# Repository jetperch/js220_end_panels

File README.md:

# Joulescope Front Panels

Welcome to Joulescope™ JS220 front panel hardware design project.  This project 
contains the open source hardware designs for a variety of JS220 front
panels.  These front panels customize Joulescope so that it can more easily 
connect to your power supply and target device.
For more information on Joulescope, see 
[www.joulescope.com](https://www.joulescope.com).

The [Baseline PDF](eagle/fp_baseline/fp_baseline.pdf) show the board outline
and critical dimensions.

The 2x3 connector to the main board is
[Samtec TSM-103-01-S-DV-A](https://www.samtec.com/products/tsm-103-01-s-dv-a)
([Mouser](https://www.mouser.com/ProductDetail/Samtec/TSM-103-01-S-DV-A?qs=0lQeLiL1qyYnWtGorwZW9A%3D%3D),
[Digi-Key](https://www.digikey.com/en/products/detail/TSM-103-01-S-DV-A/TSM-103-01-S-DV-A-ND/2685555))

The boards have been fabricated using PCBWay. 
Here are the order notes ([example](pcbway_order.png)):

* Size: 95 x 24.7 mm
* FR-4, TG 150-160, 1.6 thick, 6/6, 0.3 mm min hole size
* Solder Mask: Black, White silkscreen
* Surface Finish: HASL lead free, do NOT check accept ENIG substitution
* Finished Copper 1 oz

Special requests text:
The front-side surface is cosmetic.  
Reject units with scratches and blemishes.
Place all markings on back, including pcb product number.
Add flammability rating marking on back, such as 94V-0.

## License

All Joulescope front-panel designs are released under the 
permissive Apache 2.0 license.

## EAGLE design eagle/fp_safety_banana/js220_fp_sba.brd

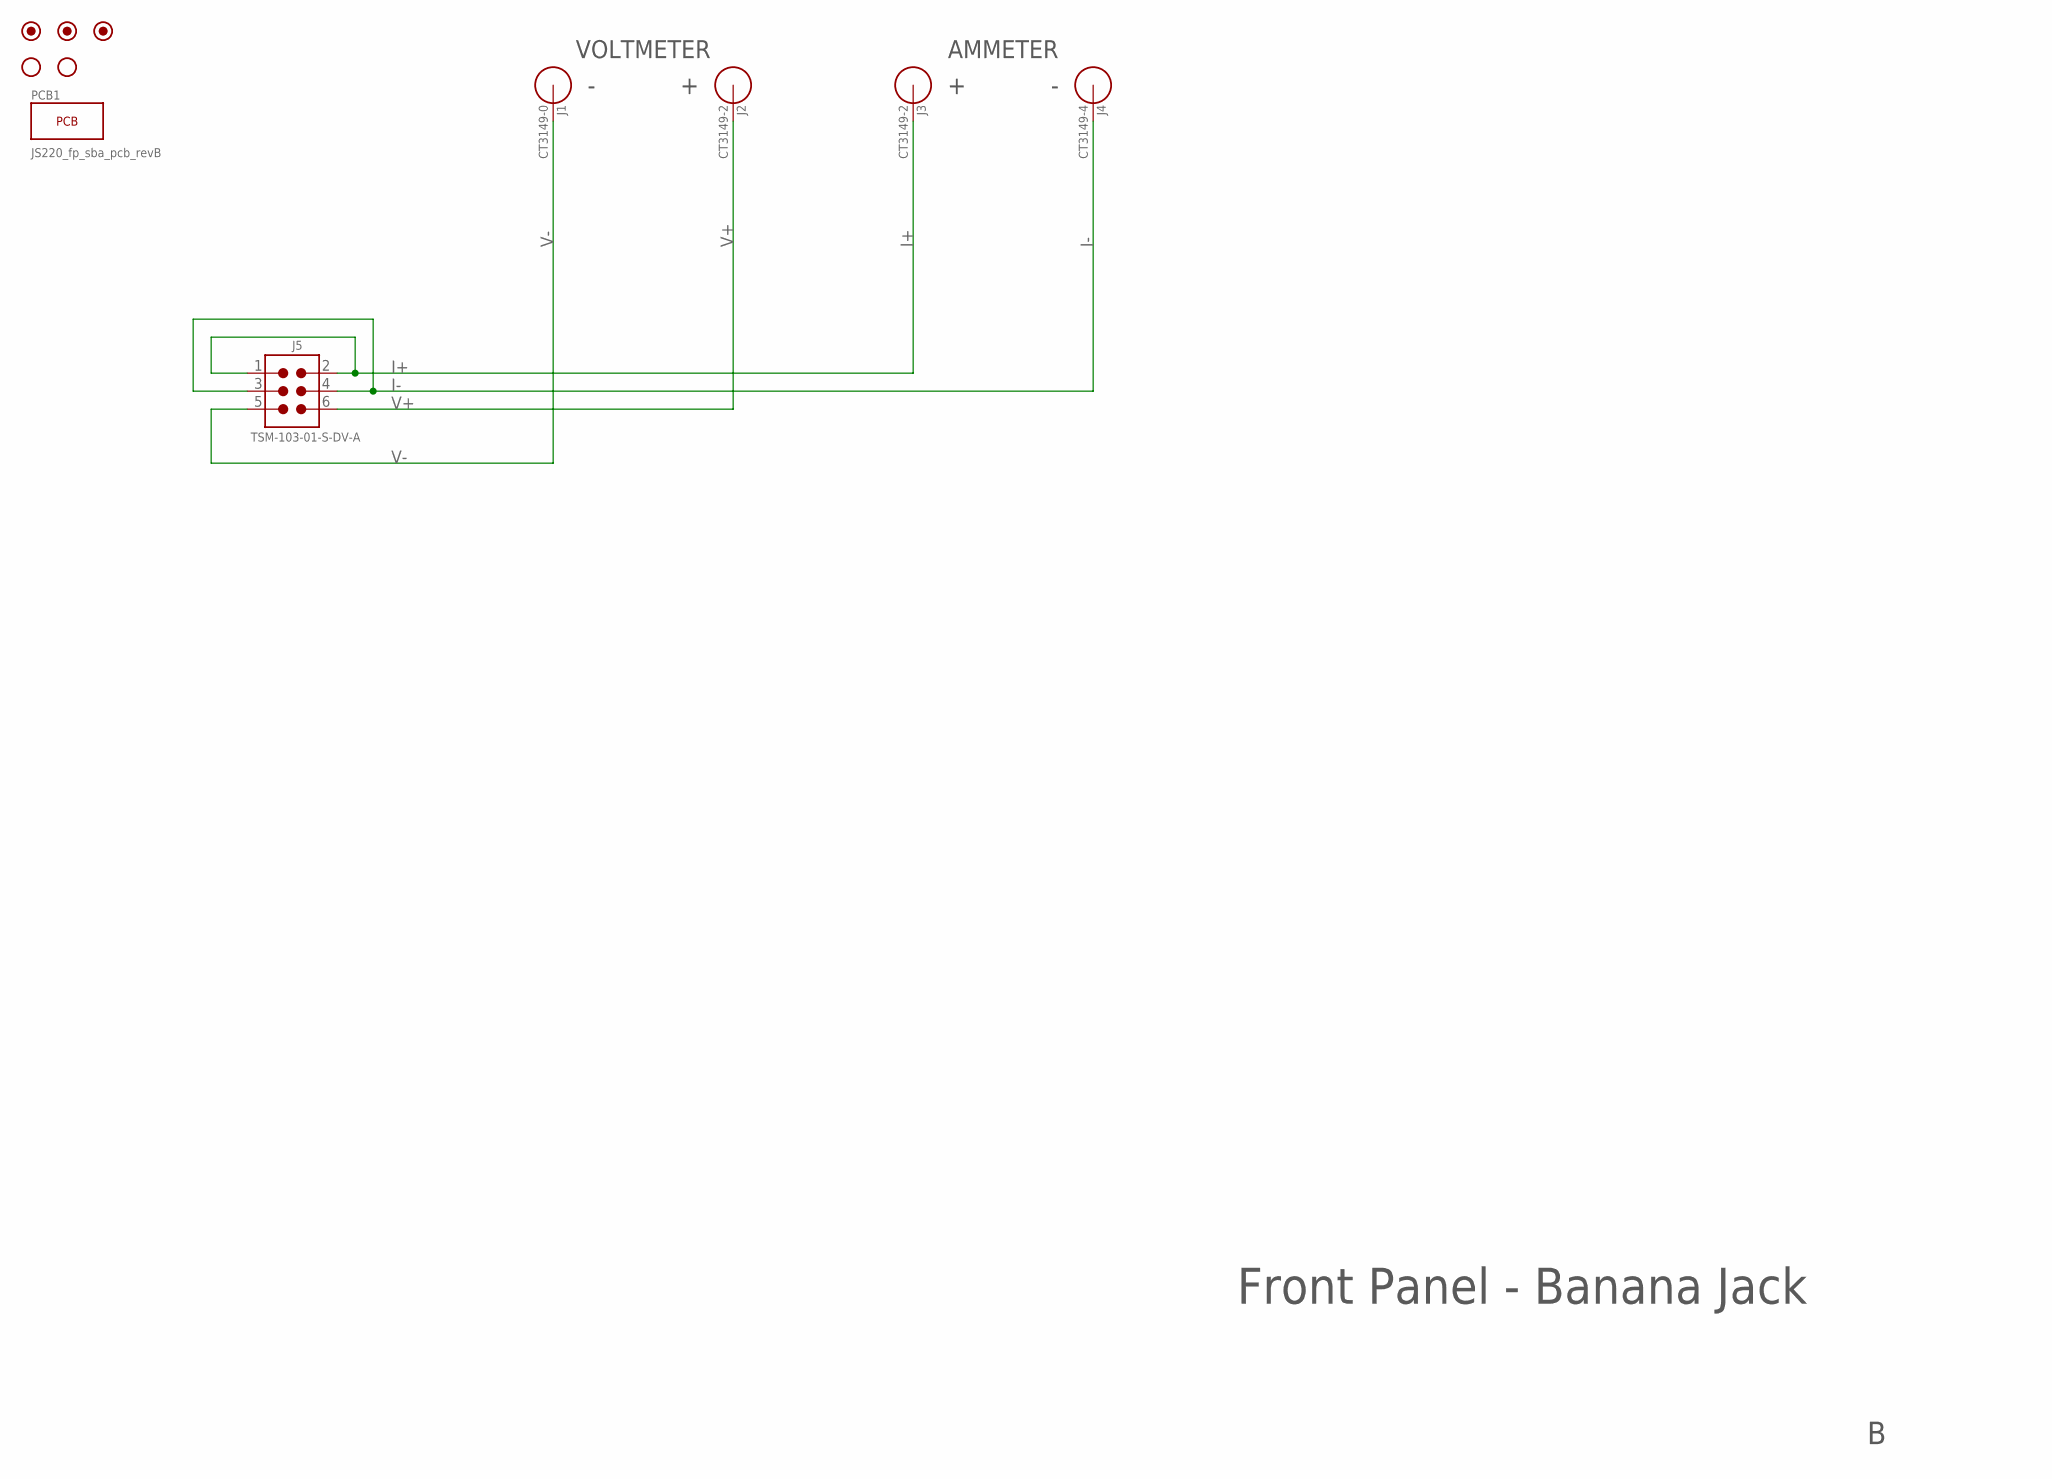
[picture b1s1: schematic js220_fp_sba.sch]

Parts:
FUD1, FUD2, FUD3: FIDUCIAL_1MM; FIDUCIAL_1MM_2MM
H1, H2: HOLE_#6_NORESTRICT; HOLE_3.5MM_NORESTRICT
J1: CT3149-0; CT3149
J2, J3: CT3149-2; CT3149
J4: CT3149-4; CT3149
J5: TSM-103-01-S-DV-A; CONN_0.1_3X2_MSA; MPN TSM-103-01-S-DV-A

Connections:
I+: J3.A, J5.1, J5.2
I-: J4.A, J5.3, J5.4
V+: J2.A, J5.6
V-: J1.A, J5.5

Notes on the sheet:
Front Panel - Banana Jack
+ -
AMMETER
VOLTMETER
- +

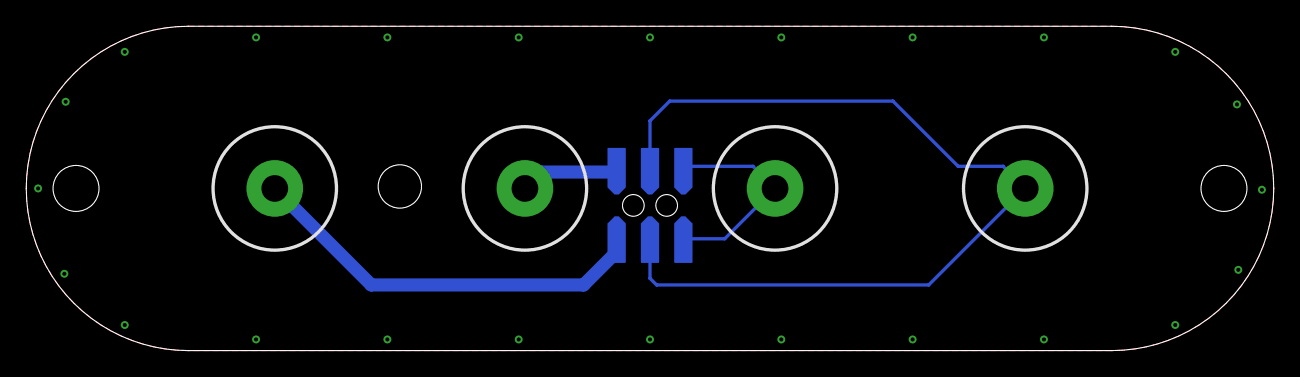
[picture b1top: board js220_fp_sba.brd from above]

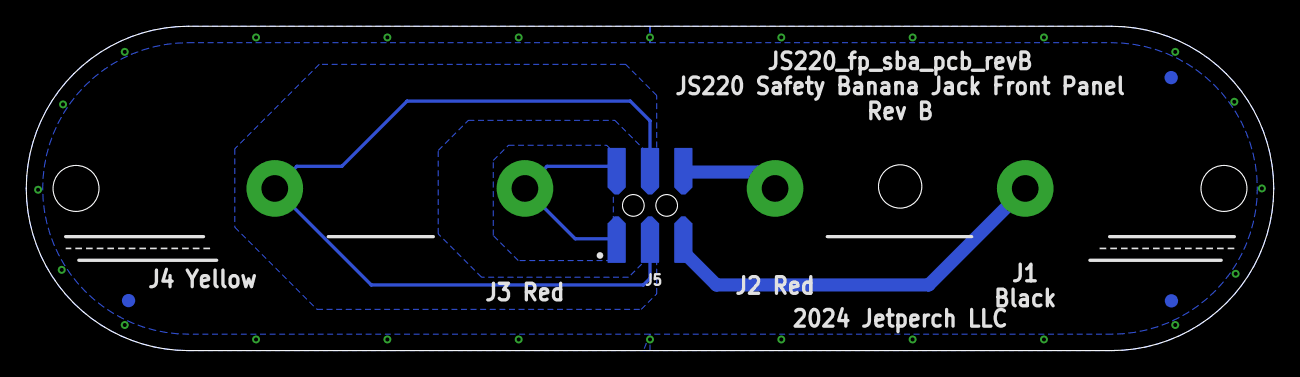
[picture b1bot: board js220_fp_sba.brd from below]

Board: 2 copper layers, 95.0 x 24.7 mm, 10 parts (4 on the bottom side), 4 nets.

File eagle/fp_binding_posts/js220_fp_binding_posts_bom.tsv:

Quantity	Part	Designators
2	111-0702-001	J2,J3
1	111-0703-001	J1
1	111-0707-001	J4
1	TSM-103-01-S-DV-A	J5
1	JS220_fp_binding_post_pcb_revC	PCB1

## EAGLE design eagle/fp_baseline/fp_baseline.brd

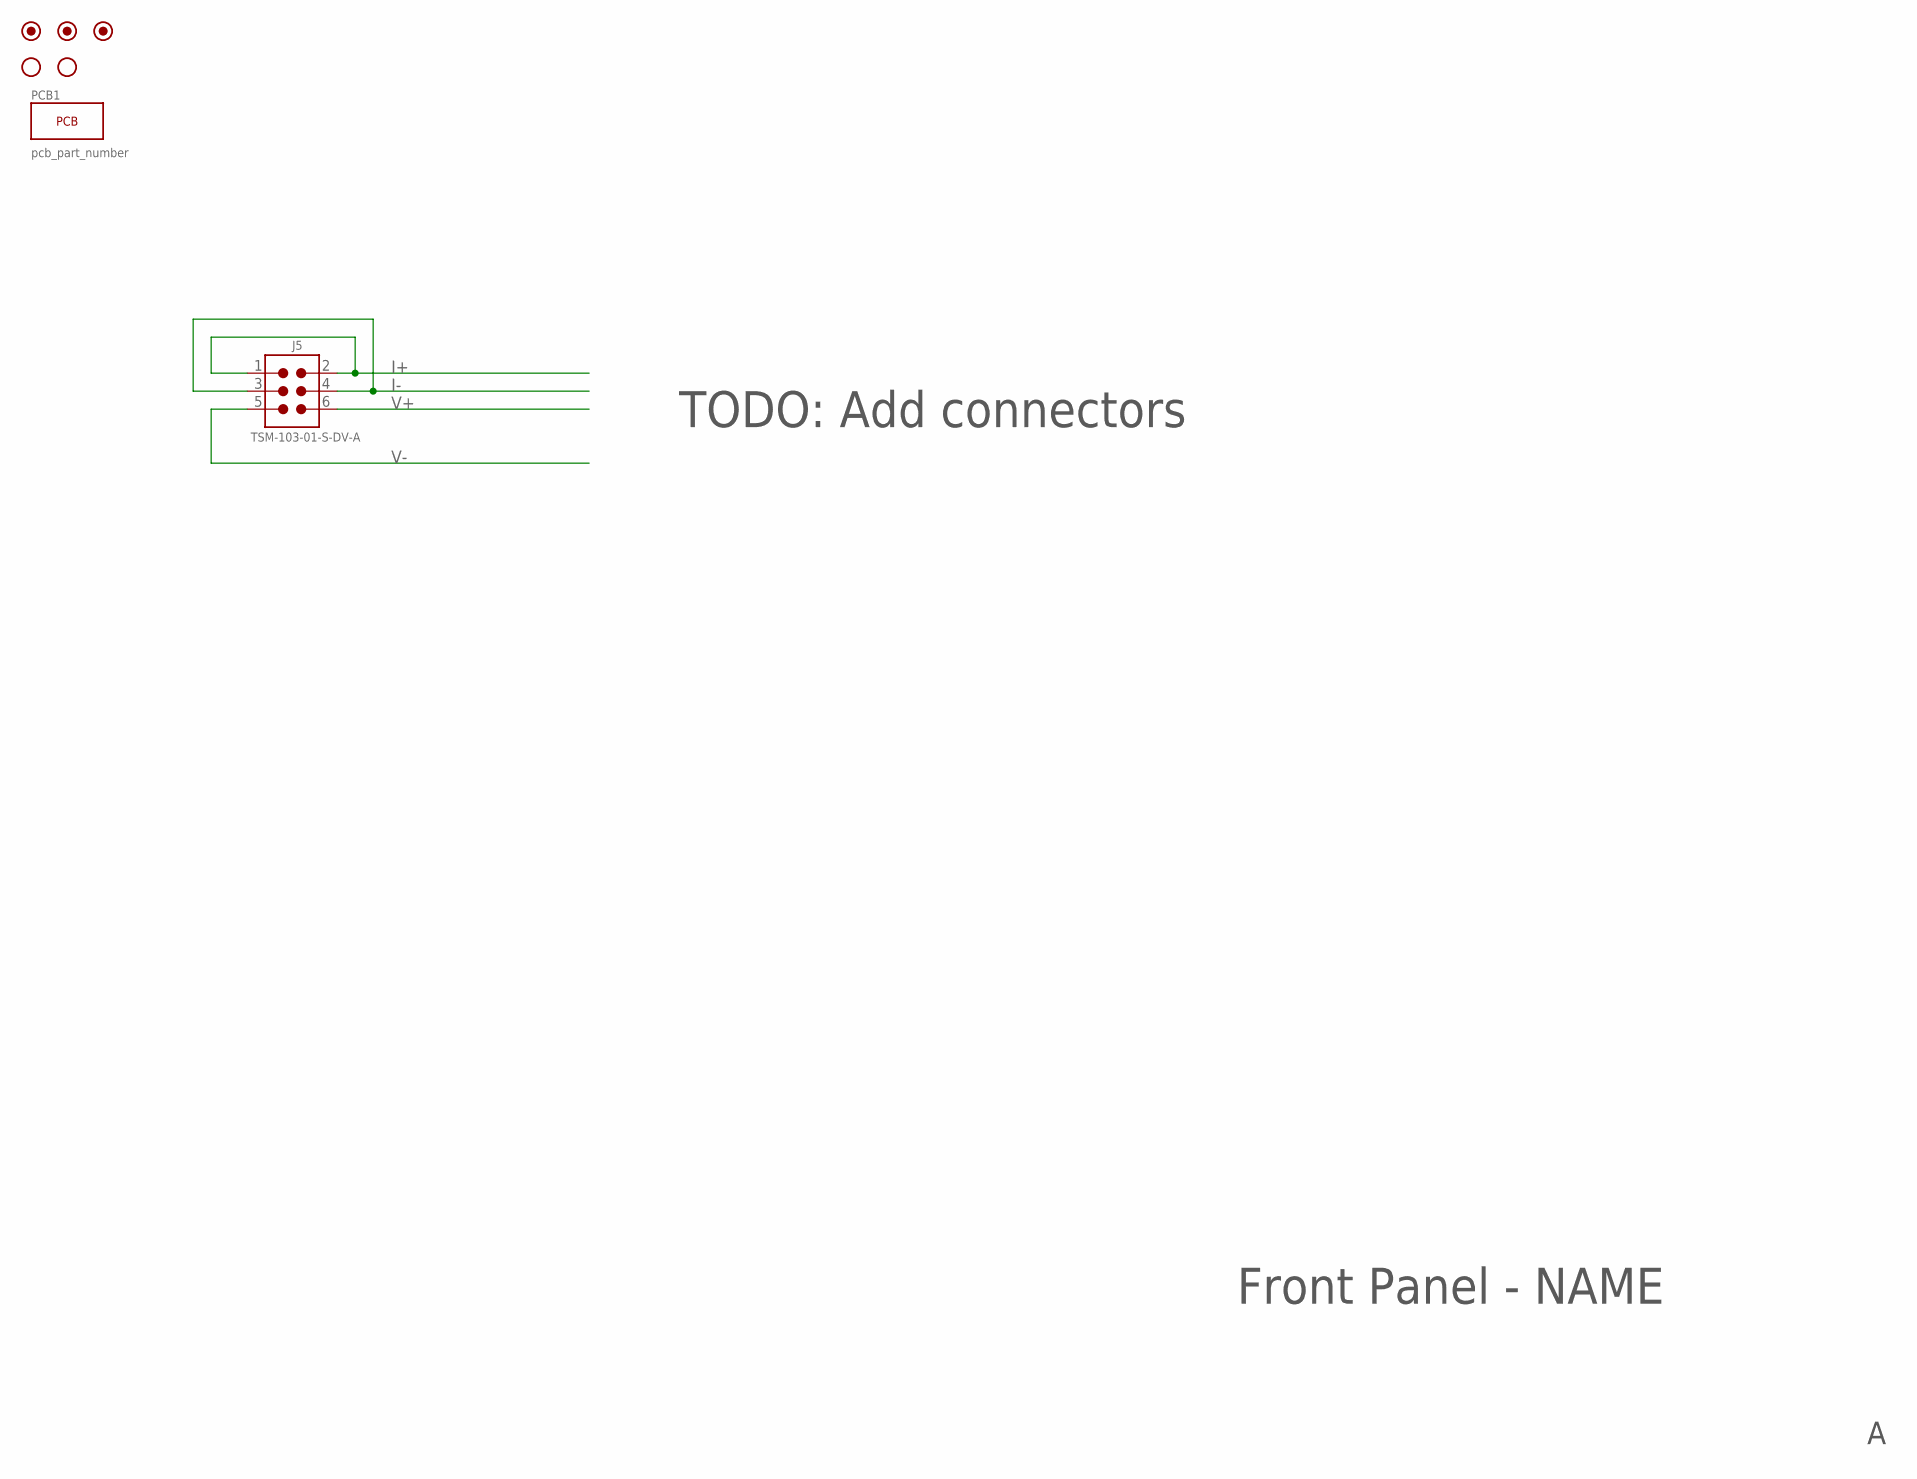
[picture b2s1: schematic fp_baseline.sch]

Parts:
FUD1, FUD2, FUD3: FIDUCIAL_1MM; FIDUCIAL_1MM_2MM
H1, H2: HOLE_#6_NORESTRICT; HOLE_3.5MM_NORESTRICT
J5: TSM-103-01-S-DV-A; CONN_0.1_3X2_MSA; MPN TSM-103-01-S-DV-A

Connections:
I+: J5.1, J5.2
I-: J5.3, J5.4
V+: J5.6
V-: J5.5

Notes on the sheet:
Front Panel - NAME
TODO: Add connectors

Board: 2 copper layers, 6 parts (4 on the bottom side), 2 nets, no tracks yet.

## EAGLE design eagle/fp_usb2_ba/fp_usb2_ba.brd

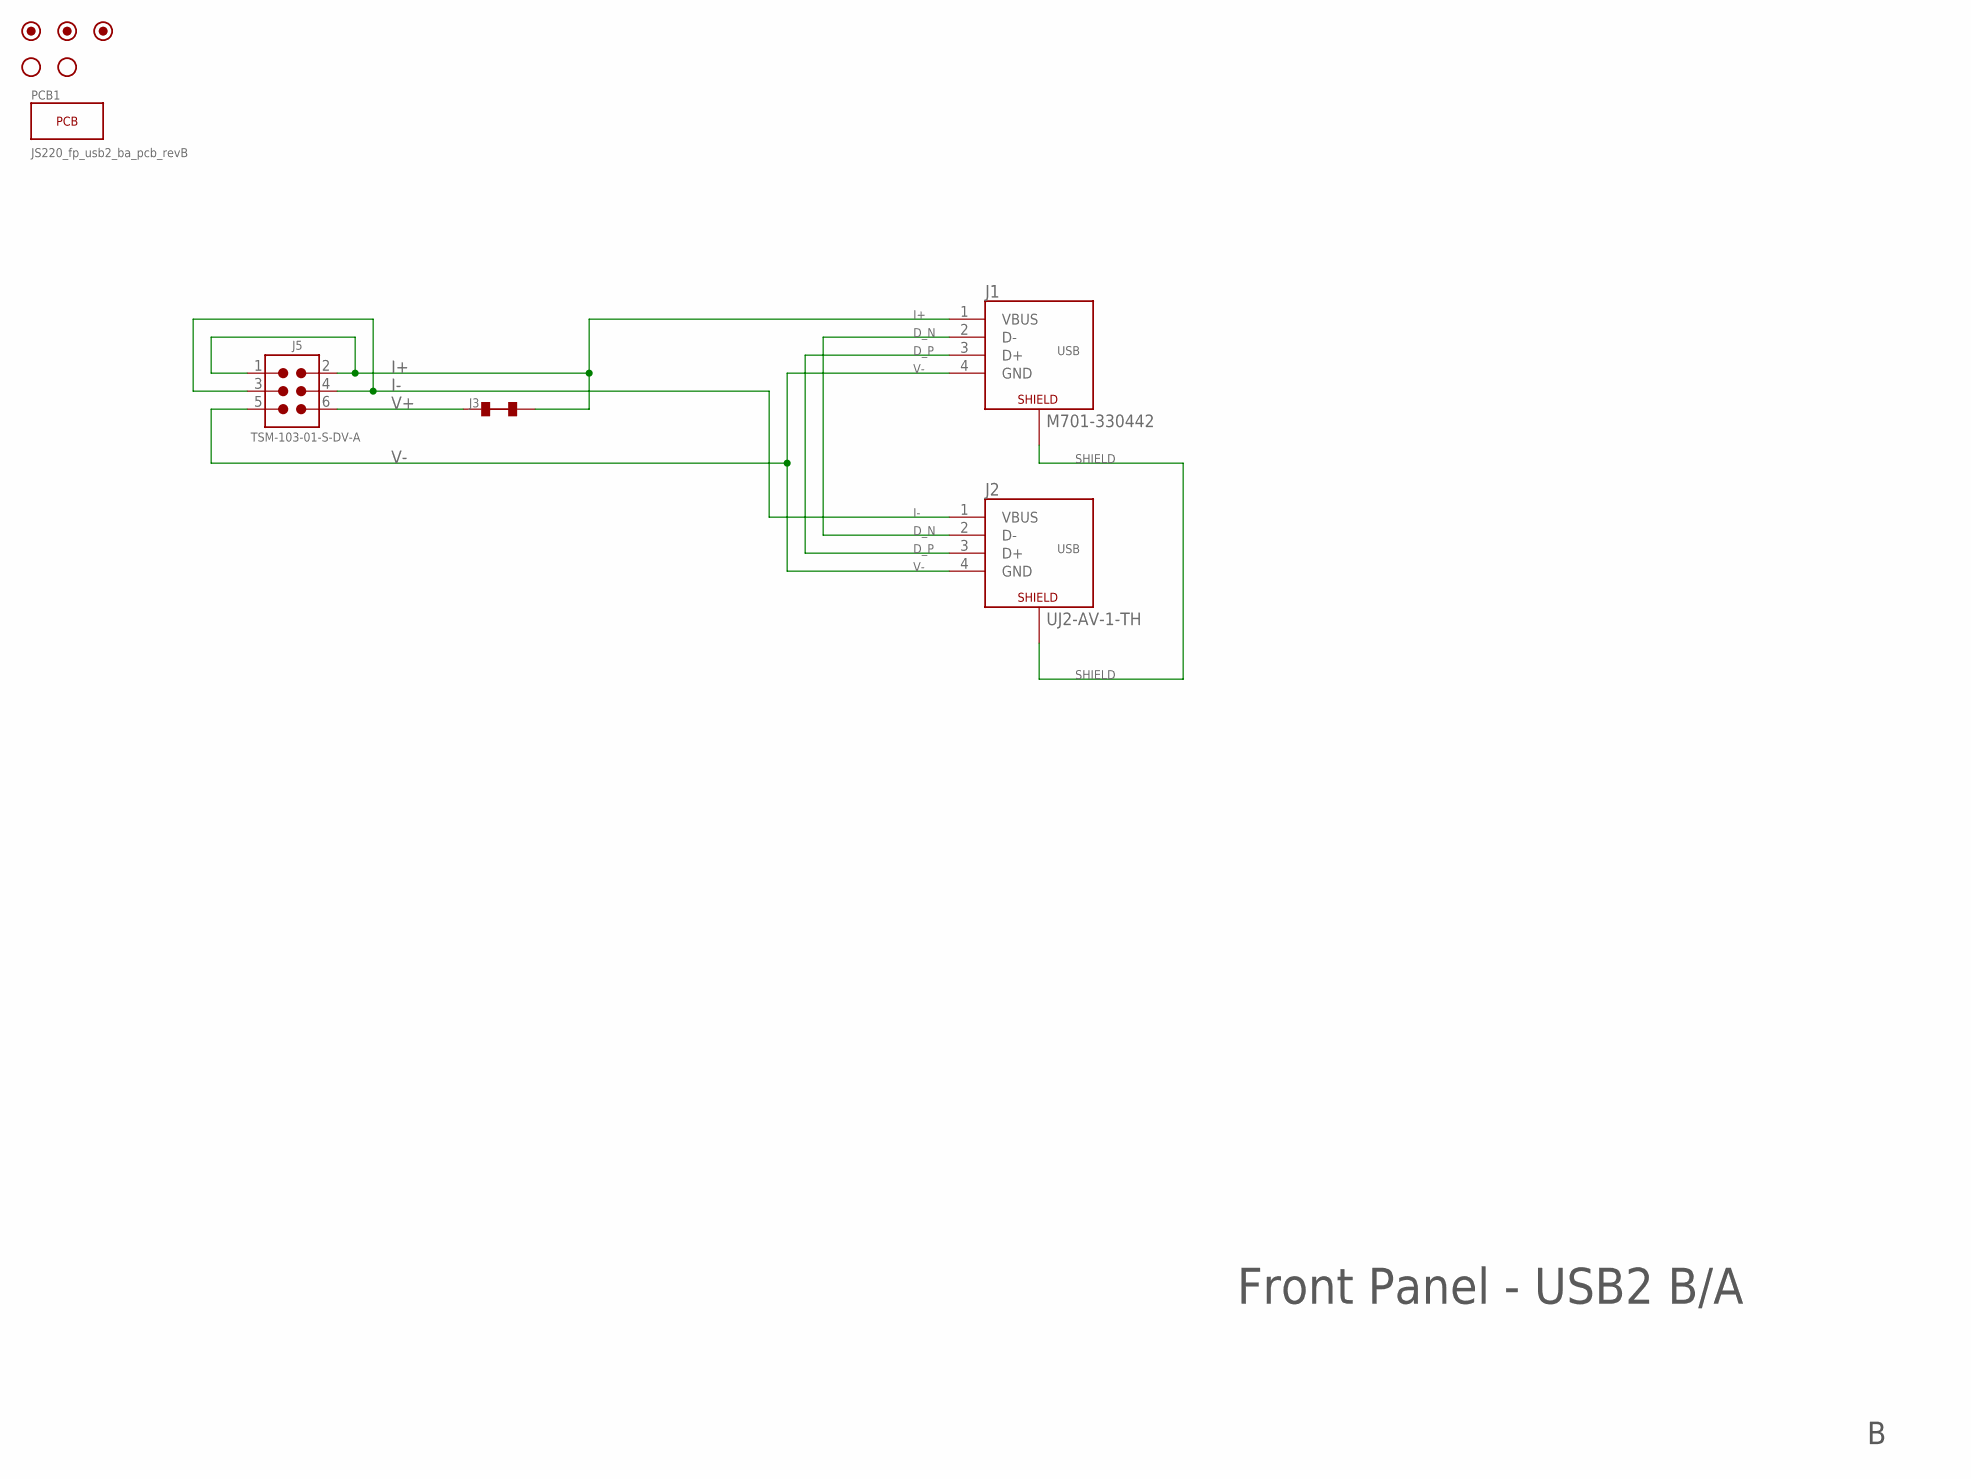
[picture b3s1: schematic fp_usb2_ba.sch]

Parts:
FUD1, FUD2, FUD3: FIDUCIAL_1MM; FIDUCIAL_1MM_2MM
H1, H2: HOLE_#6_NORESTRICT; HOLE_3.5MM_NORESTRICT
J1: M701-330442; USB-B-VTH
J2: UJ2-AV-1-TH; USB-A-VTH
J3: TRACE_CUT0603; J0603
J5: TSM-103-01-S-DV-A; CONN_0.1_3X2_MSA; MPN TSM-103-01-S-DV-A

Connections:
D_N: J1.2 (D-), J2.2 (D-)
D_P: J1.3 (D+), J2.3 (D+)
I+: J1.1 (VBUS), J3.2, J5.1, J5.2
I-: J2.1 (VBUS), J5.3, J5.4
SHIELD: J1.SHIELD@1 (SHIELD), J1.SHIELD@3 (SHIELD), J2.SHIELD@1 (SHIELD), J2.SHIELD@3 (SHIELD)
V+: J3.1, J5.6
V-: J1.4 (GND), J2.4 (GND), J5.5

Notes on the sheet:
Front Panel - USB2 B/A

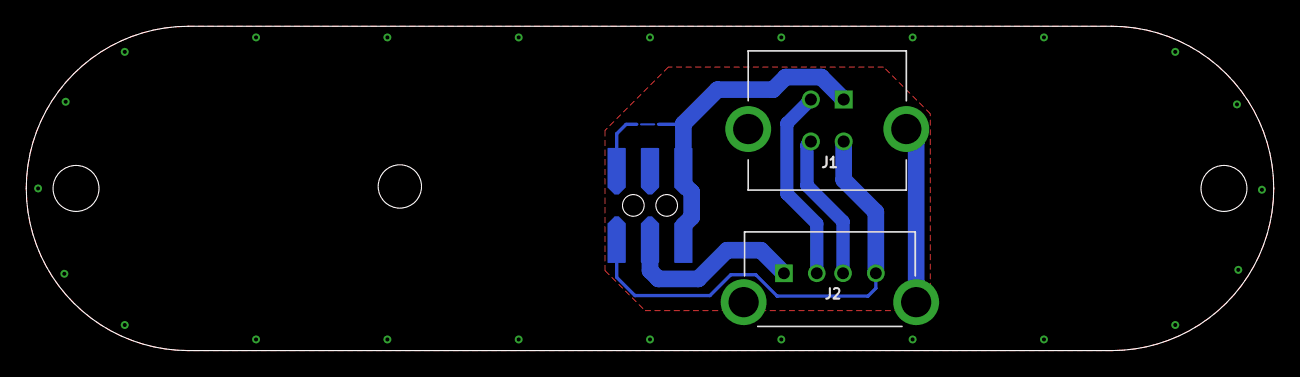
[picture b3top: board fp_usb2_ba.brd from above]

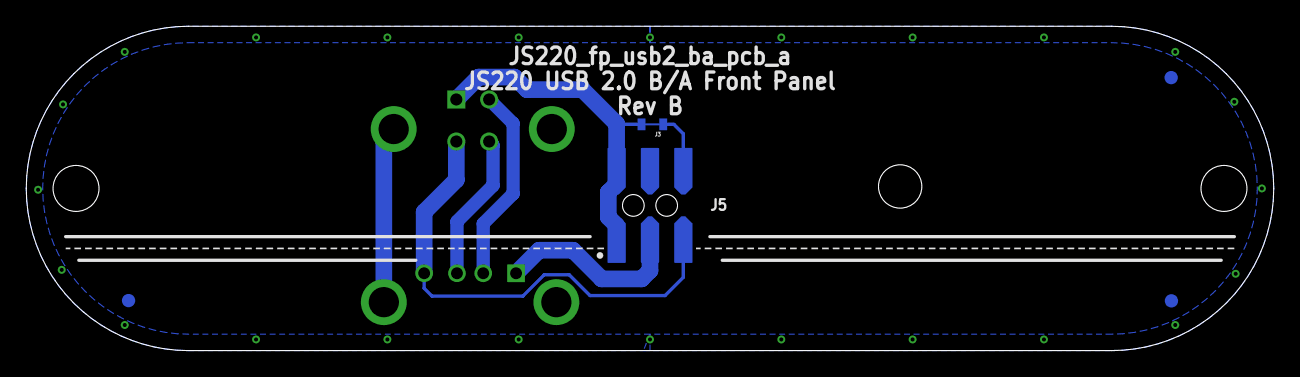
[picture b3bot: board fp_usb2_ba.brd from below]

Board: 2 copper layers, 95.0 x 24.7 mm, 9 parts (5 on the bottom side), 7 nets.

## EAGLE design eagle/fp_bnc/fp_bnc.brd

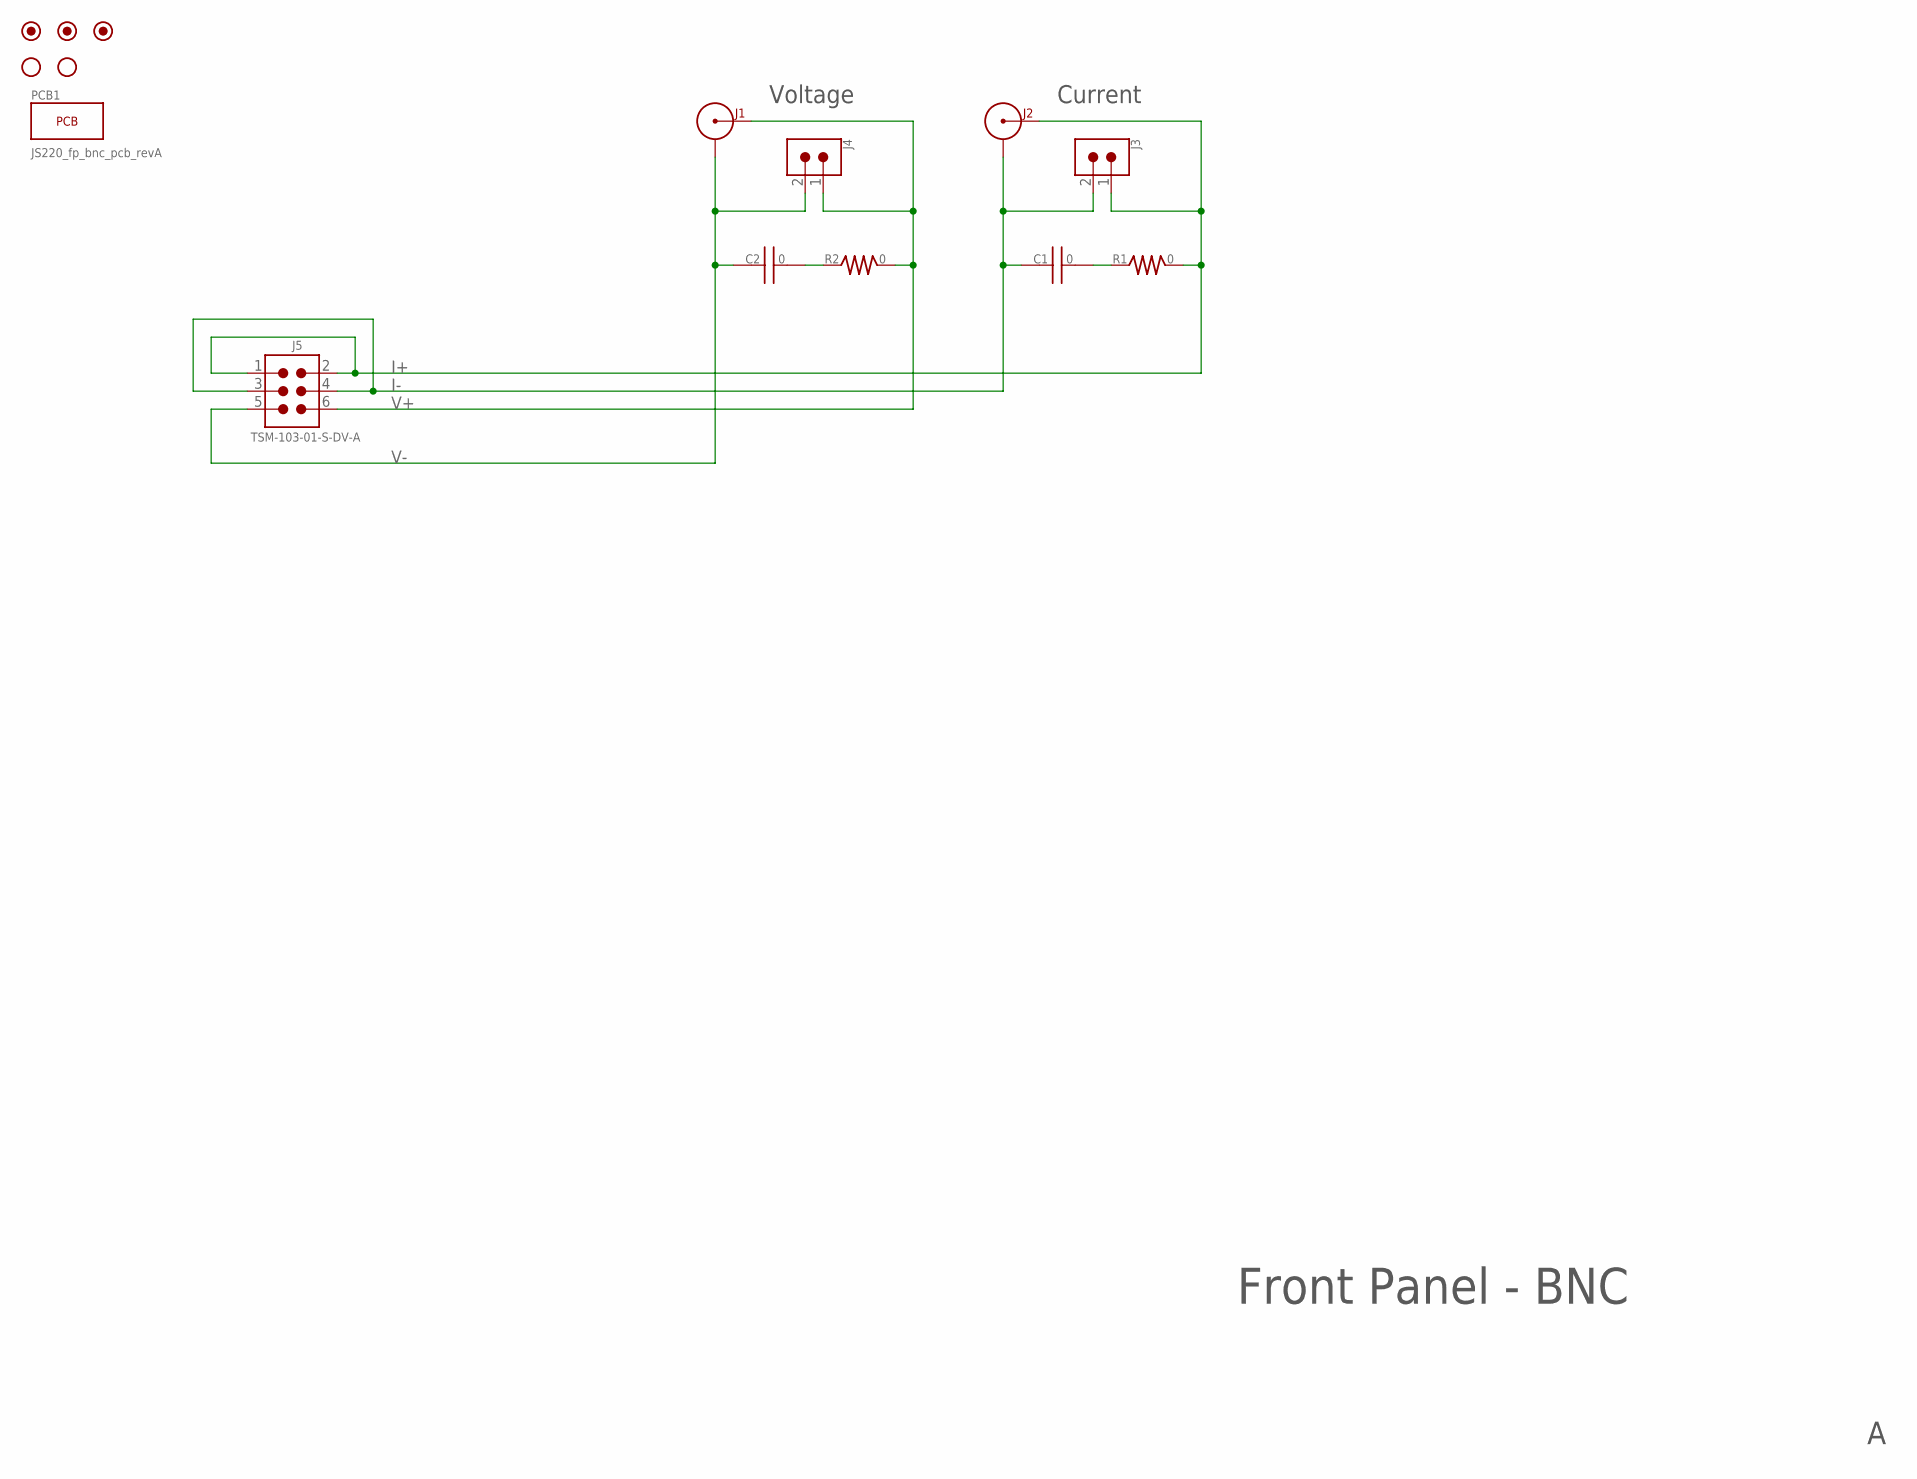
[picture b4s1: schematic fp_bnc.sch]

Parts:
C1, C2: 0; 0603
FUD1, FUD2, FUD3: FIDUCIAL_1MM; FIDUCIAL_1MM_2MM
H1, H2: HOLE_#6_NORESTRICT; HOLE_3.5MM_NORESTRICT
J1, J2: 031-5329-52RFX; BNC_31-5329-52RFX; MPN 031-5329-52RFX
J3, J4: CONN_0.1_2X1; CONN_0.1_2X1_M
J5: TSM-103-01-S-DV-A; CONN_0.1_3X2_MSA; MPN TSM-103-01-S-DV-A
R1, R2: 0; 1206; TOLERANCE 1%

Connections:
I+: J2.SIGNAL, J3.1, J5.1, J5.2, R1.2
I-: C1.1, J2.G@1 (SHIELD), J2.G@2 (SHIELD), J2.G@3 (SHIELD), J2.G@4 (SHIELD), J3.2, J5.3, J5.4
I_T: C1.2, R1.1
V+: J1.SIGNAL, J4.1, J5.6, R2.2
V-: C2.1, J1.G@1 (SHIELD), J1.G@2 (SHIELD), J1.G@3 (SHIELD), J1.G@4 (SHIELD), J4.2, J5.5
V_T: C2.2, R2.1

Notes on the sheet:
Front Panel - BNC
Voltage
Current

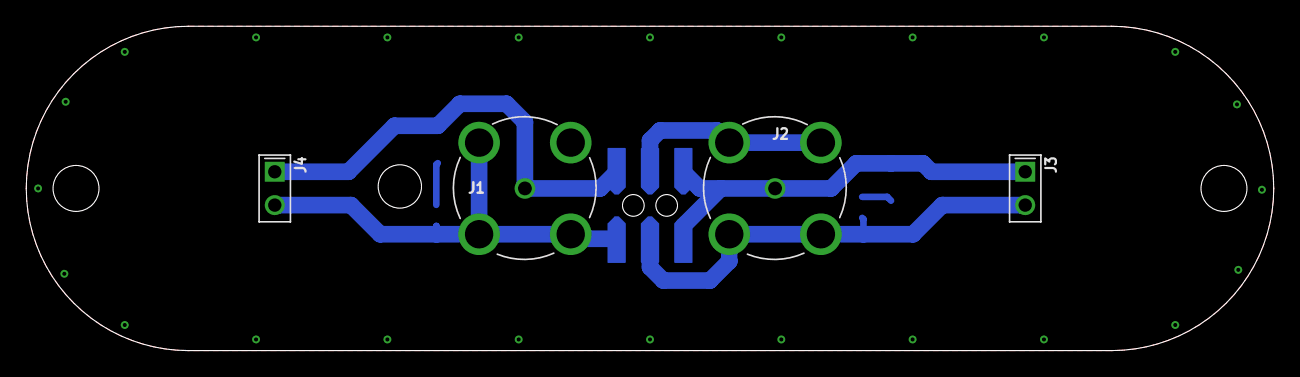
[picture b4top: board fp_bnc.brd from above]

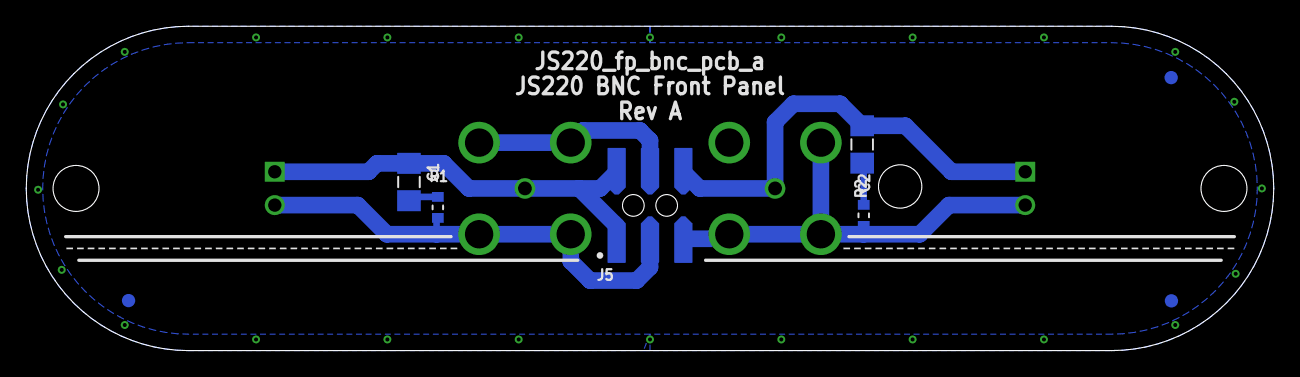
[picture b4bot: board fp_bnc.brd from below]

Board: 2 copper layers, 95.0 x 24.7 mm, 14 parts (8 on the bottom side), 6 nets.

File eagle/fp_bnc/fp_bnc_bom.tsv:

Quantity	Part	Designators
2	031-5329-52RFX	J1,J2
1	TSM-103-01-S-DV-A	J5
1	JS220_fp_bnc_pcb_revA	PCB1

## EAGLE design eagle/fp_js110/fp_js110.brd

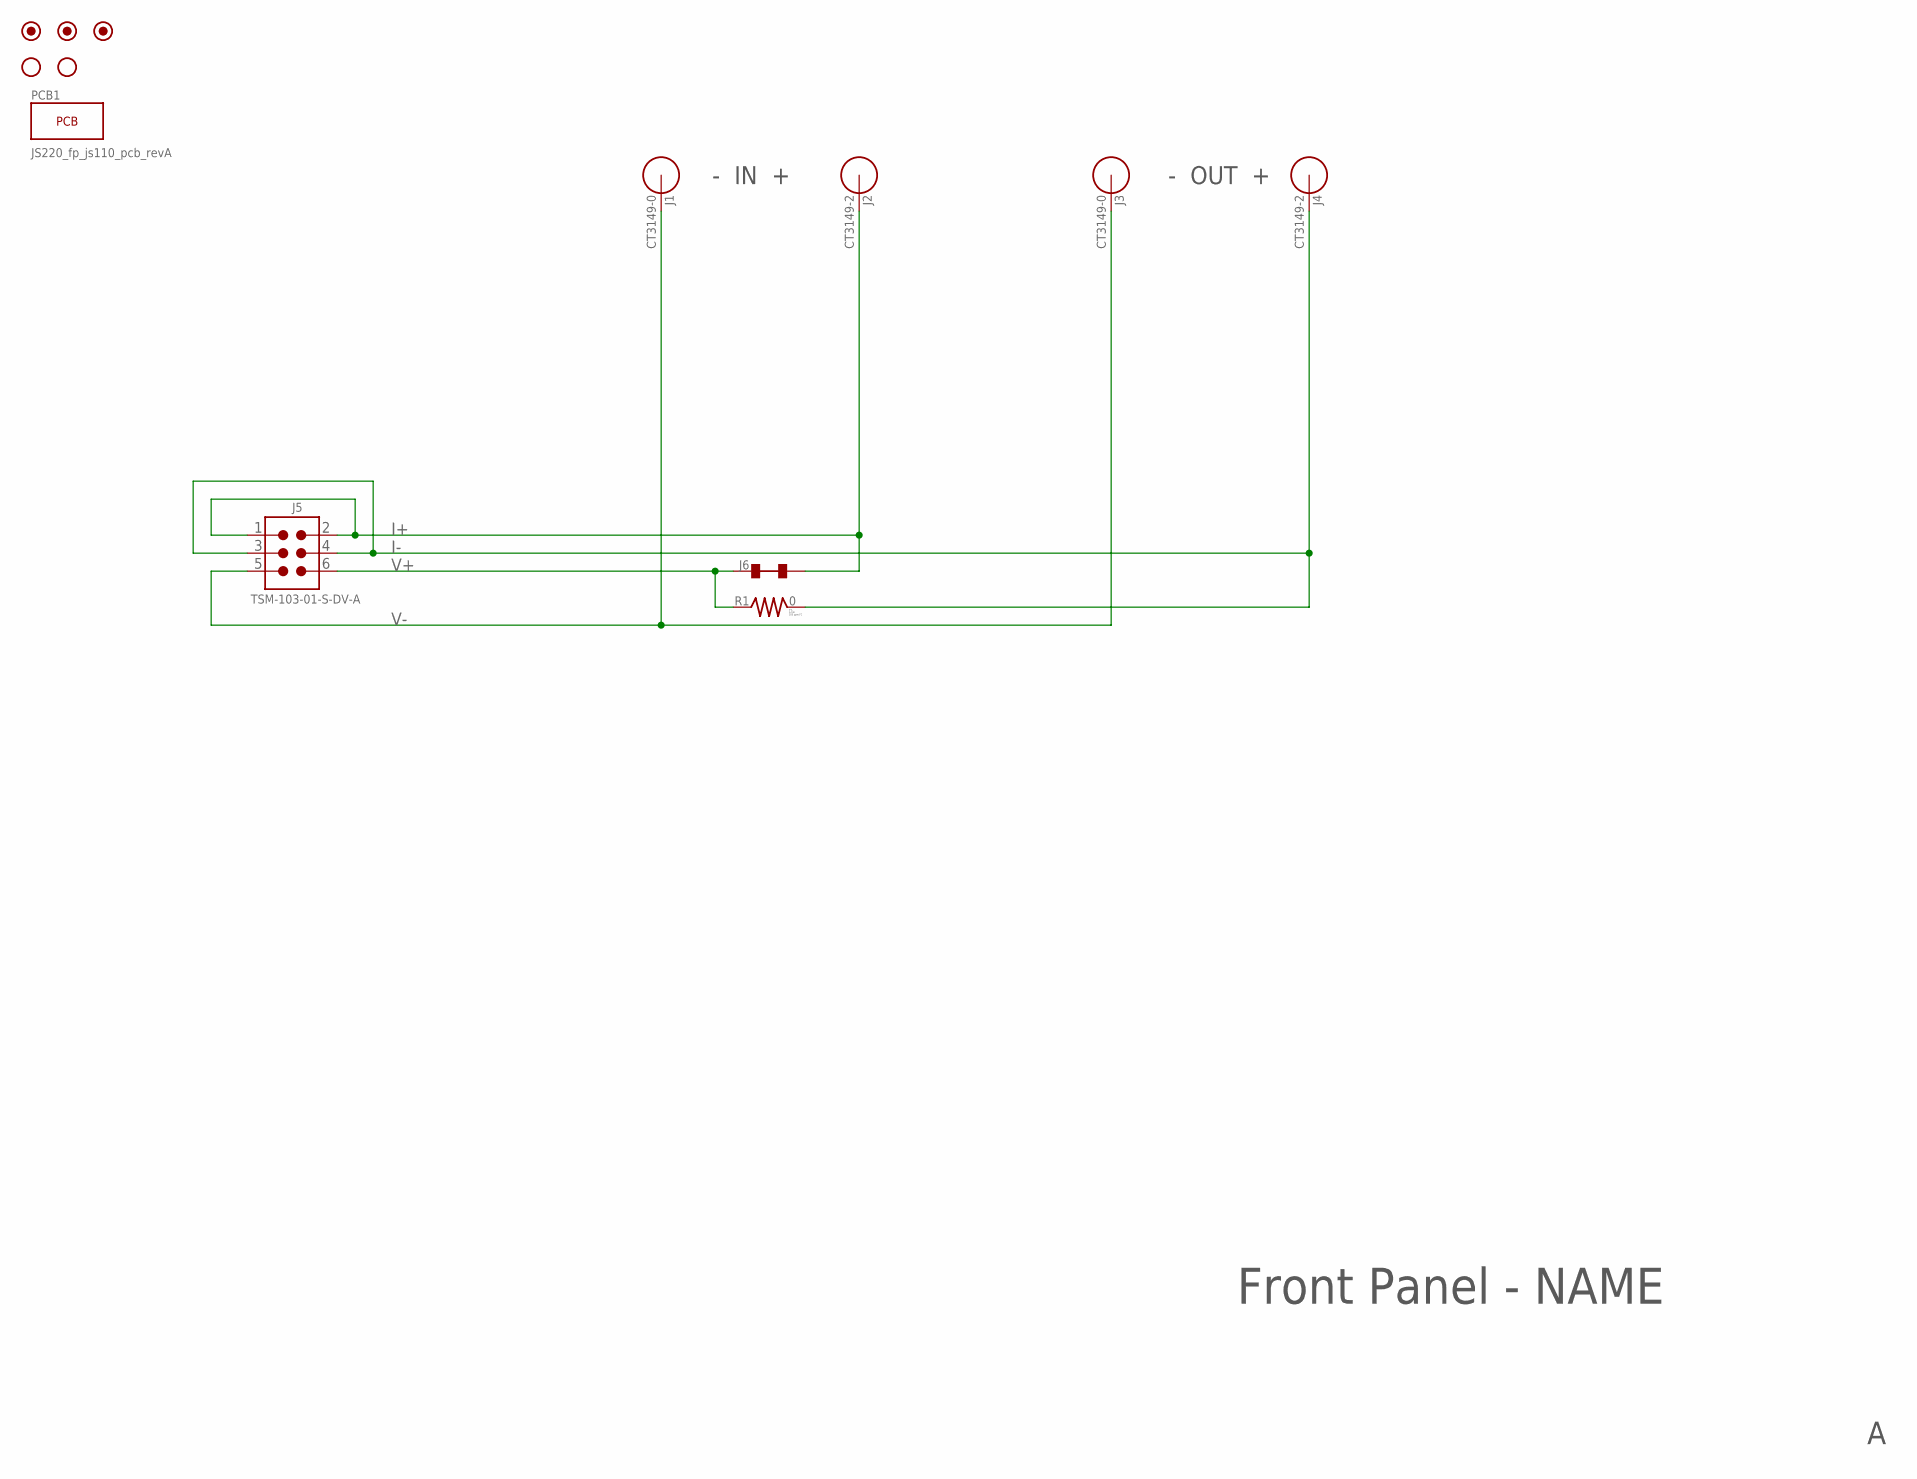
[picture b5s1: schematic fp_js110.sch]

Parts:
FUD1, FUD2, FUD3: FIDUCIAL_1MM; FIDUCIAL_1MM_2MM
H1, H2: HOLE_#6_NORESTRICT; HOLE_3.5MM_NORESTRICT
J1, J3: CT3149-0; CT3149
J2, J4: CT3149-2; CT3149
J5: TSM-103-01-S-DV-A; CONN_0.1_3X2_MSA; MPN TSM-103-01-S-DV-A
J6: TRACE_CUT0603; J0603
R1: 0; 0603

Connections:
I+: J2.A, J5.1, J5.2, J6.2
I-: J4.A, J5.3, J5.4, R1.2
V+: J5.6, J6.1, R1.1
V-: J1.A, J3.A, J5.5

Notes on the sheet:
Front Panel - NAME
- IN +
- OUT +

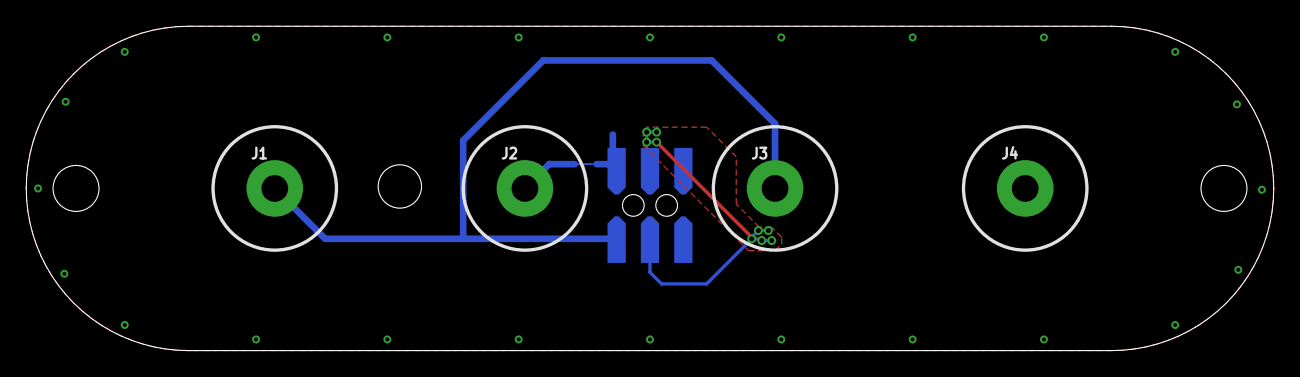
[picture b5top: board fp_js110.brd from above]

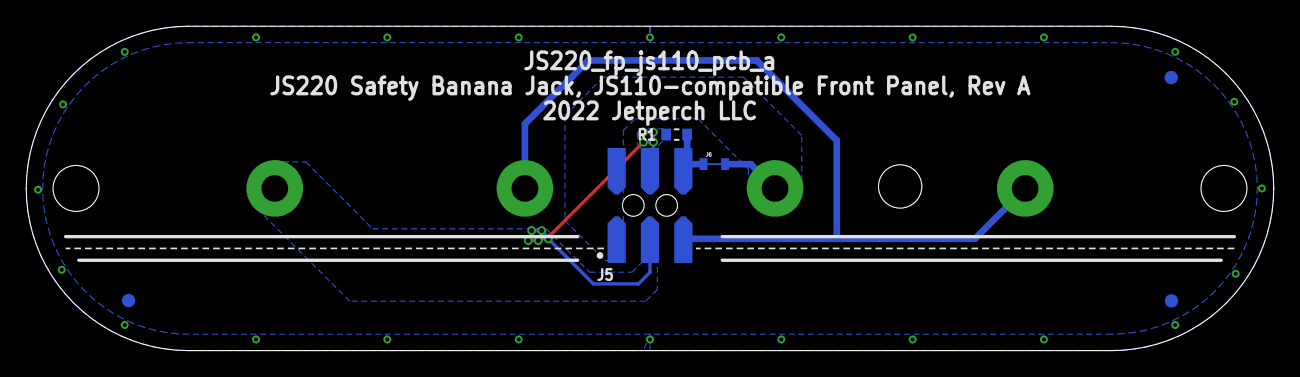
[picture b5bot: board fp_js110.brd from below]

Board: 2 copper layers, 95.0 x 24.7 mm, 12 parts (6 on the bottom side), 4 nets.

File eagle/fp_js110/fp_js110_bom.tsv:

Quantity	Part	Designators
2	CT3149-0	J1,J3
2	CT3149-2	J2,J4
1	TSM-103-01-S-DV-A	J5
1	JS220_fp_js110_pcb_revA	PCB1
